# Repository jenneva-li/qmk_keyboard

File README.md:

# Split Keyboard

This is a fully customizable split mechanical keyboard featuring per-key RGB lighting, dual 2.2″ LCD displays, and complete QMK firmware support.

> **Note:** This project is currently under development. Detailed build instructions and documentation will be provided soon.

## Features

- **Ergonomic Split Layout** – Improves typing comfort and reduces strain.  
- **Dual LCD Displays** – Each half includes a 2.2" LCD for customizable graphics and real-time system information.
- **QMK Firmware** – Fully programmable, with support for layers, macros, and custom keymaps.  
- **Per-Key RGB Lighting** – Individually addressable SK6812 Mini LEDs for lighting effects.  
- **Hot-Swappable Switches** – Easily swap switches without soldering.  

## Specifications

- **Microcontroller**: STM32G474CETx
- **Key Layout**: Split layout with additional keys for layers and macros.
- **Display**: 2.2" LCD (320x240 resolution) per half.
- **Lighting**: SK6812 Mini RGB LEDs.
- **Switches**: Kailh Choc Low Profile.

## Build & Assembly

1. Order the PCBs and have them assembled using the provided BOM and pick-and-place files (e.g., via PCBWay).
2. 3D print the keyboard case components and source all necessary hardware, including LCDs, switches, keycaps, and mounting hardware.
3. Assemble all components, ensuring proper alignment of the PCB, switches, and case.
4. Flash the appropriate firmware onto each half of the keyboard. Note that the left and right halves require separate firmware builds.

## Roadmap
> This section outlines the planned features and improvements for the project. It is a work in progress and will be updated as development continues.

- [ ] Finalize PCB design  
- [ ] Publish detailed step-by-step build guide  
- [ ] Write firmware flashing and setup documentation  
- [ ] Upload STL files for 3D-printable case components  
- [ ] Publish demo and assembly videos

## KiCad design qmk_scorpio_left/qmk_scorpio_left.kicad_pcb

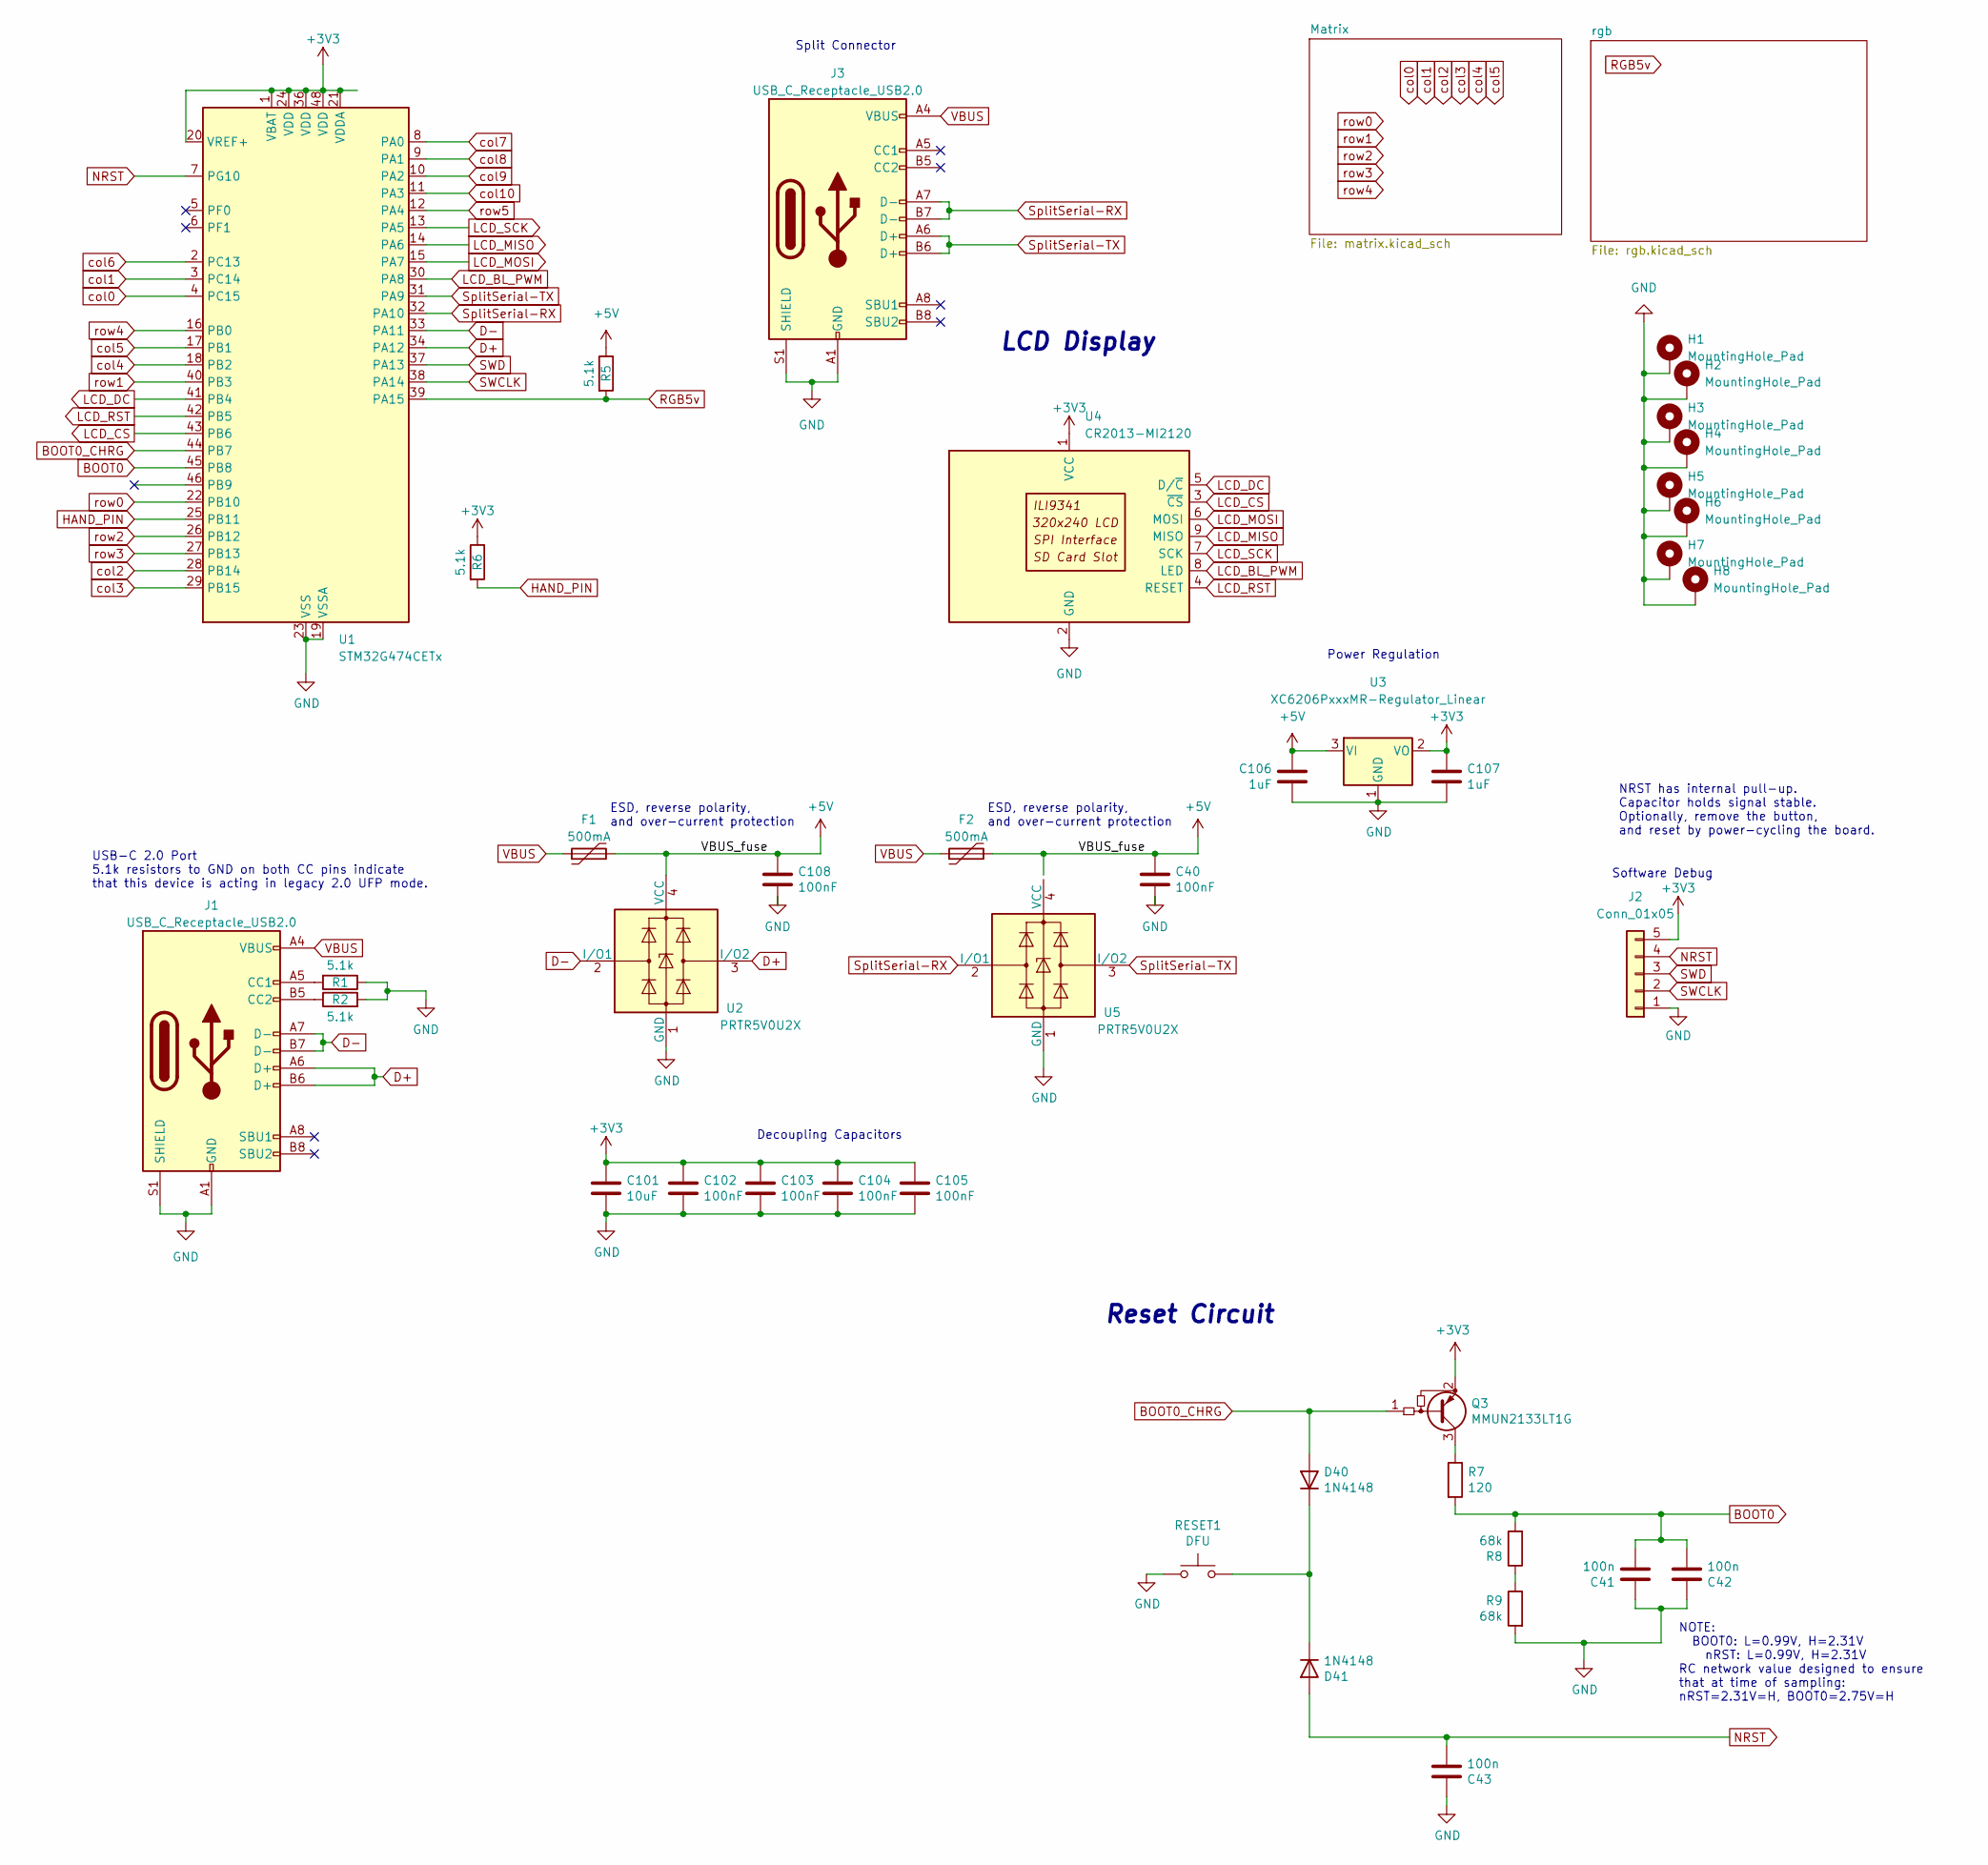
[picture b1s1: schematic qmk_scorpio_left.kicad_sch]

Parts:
C40, C102, C103, C104, C105, C108: 100nF; C_0402_1005Metric; LCSC C307331
C41, C42, C43: 100n; C_0805_2012Metric
C101: 10uF; C_0603_1608Metric; LCSC C307331
C106, C107: 1uF; C_0402_1005Metric; LCSC C307331
D40, D41: 1N4148; D_SOD-123
F1, F2: 500mA; Fuse_1206_3216Metric; LCSC C135341
H1, H2, H3, H4, H5, H6, H7, H8: MountingHole_Pad; MountingHole_3.2mm_M3_DIN965_Pad
J1, J3: USB_C_Receptacle_USB2.0; USB_C_Receptacle_HRO_TYPE-C-31-M-14; JlcRotOffset 180
J2: Conn_01x05; PinHeader_1x05_P2.54mm_Vertical
Q3: MMUN2133LT1G; SOT-23-3
R1, R2, R5, R6: 5.1k; R_0402_1005Metric
R7: 120; R_0805_2012Metric
R8, R9: 68k; R_0805_2012Metric
RESET1: DFU; SW_SPST_TL3342
U1: STM32G474CETx; LQFP-48_7x7mm_P0.5mm
U2, U5: PRTR5V0U2X; SOT-143; LCSC C2827688
U3: XC6206PxxxMR-Regulator_Linear; SOT-23; LCSC C5446
U4: CR2013-MI2120

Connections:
+3V3: C101.1, C102.1, C103.1, C104.1, C105.1, C107.1, J2.5, Q3.2 (E), R6.1, U1.1 (VBAT), U1.20 (VREF+), U1.21 (VDDA), U1.24 (VDD), U1.36 (VDD), U1.48 (VDD), U3.2 (VO), U4.1 (VCC)
+5V: C40.1, C106.1, C108.1, F1.2, F2.2, R5.1, U2.4 (VCC), U3.3 (VI); also elsewhere on the board
BOOT0: C41.2, C42.2, R7.2, R8.2, U1.45 (PB8)
BOOT0_CHRG: D40.2 (A), Q3.1 (B), U1.44 (PB7)
D+: J1.A6 (D+), J1.B6 (D+), U1.34 (PA12), U2.3 (I/O2)
D-: J1.A7 (D-), J1.B7 (D-), U1.33 (PA11), U2.2 (I/O1)
GND: C40.2, C41.1, C42.1, C43.1, C101.2, C102.2, C103.2, C104.2, C105.2, C106.2, C107.2, C108.2, H1.1, H2.1, H3.1, H4.1, H5.1, H6.1, H7.1, H8.1, J1.A1 (GND), J1.A12 (GND), J1.B1 (GND), J1.B12 (GND), J1.S1 (SHIELD), J2.1, J3.A1 (GND), J3.A12 (GND), J3.B1 (GND), J3.B12 (GND), J3.S1 (SHIELD), R1.1, R2.2, R9.2, RESET1.1, U1.19 (VSSA), U1.23 (VSS), U1.35 (VSS), U1.47 (VSS), U2.1 (GND), U3.1 (GND), U4.2 (GND), U5.1 (GND); also elsewhere on the board
HAND_PIN: R6.2, U1.25 (PB11)
LCD_BL_PWM: U1.30 (PA8), U4.8 (LED)
LCD_CS: U1.43 (PB6), U4.3 (~CS)
LCD_DC: U1.41 (PB4), U4.5 (D/~C)
LCD_MISO: U1.14 (PA6), U4.9 (MISO)
LCD_MOSI: U1.15 (PA7), U4.6 (MOSI)
LCD_RST: U1.42 (PB5), U4.4 (RESET)
LCD_SCK: U1.13 (PA5), U4.7 (SCK)
NRST: C43.2, D41.2 (A), J2.4, U1.7 (PG10)
unnamed: D40.1 (K), D41.1 (K), RESET1.2
unnamed: J1.A5 (CC1), R1.2
unnamed: J1.B5 (CC2), R2.1
unnamed: Q3.3 (C), R7.1
unnamed: R8.1, R9.1
RGB5v: R5.2, U1.39 (PA15); also elsewhere on the board
SWCLK: J2.2, U1.38 (PA14)
SWD: J2.3, U1.37 (PA13)
SplitSerial-RX: J3.A7 (D-), J3.B7 (D-), U1.32 (PA10), U5.2 (I/O1)
SplitSerial-TX: J3.A6 (D+), J3.B6 (D+), U1.31 (PA9), U5.3 (I/O2)
VBUS: F1.1, F2.1, J1.A4 (VBUS), J1.A9 (VBUS), J1.B4 (VBUS), J1.B9 (VBUS), J3.A4 (VBUS), J3.A9 (VBUS), J3.B4 (VBUS), J3.B9 (VBUS)
col0: U1.4 (PC15); also elsewhere on the board
col1: U1.3 (PC14); also elsewhere on the board
col2: U1.28 (PB14); also elsewhere on the board
col3: U1.29 (PB15); also elsewhere on the board
col4: U1.18 (PB2); also elsewhere on the board
col5: U1.17 (PB1); also elsewhere on the board
col6: U1.2 (PC13)
col7: U1.8 (PA0)
col8: U1.9 (PA1)
col9: U1.10 (PA2)
col10: U1.11 (PA3)
row0: U1.22 (PB10); also elsewhere on the board
row1: U1.40 (PB3); also elsewhere on the board
row2: U1.26 (PB12); also elsewhere on the board
row3: U1.27 (PB13); also elsewhere on the board
row4: U1.16 (PB0); also elsewhere on the board
row5: U1.12 (PA4)

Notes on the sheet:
Decoupling Capacitors
NOTE: BOOT0: L=0.99V, H=2.31V nRST: L=0.99V, H=2.31V RC network value designed to ensure that at time of sampling: nRST=2.31V=H, BOOT0=2.75V=H
Power Regulation
Reset Circuit
USB-C 2.0 Port 5.1k resistors to GND on both CC pins indicate that this device is acting in legacy 2.0 UFP mode.
ESD, reverse polarity, and over-current protection
Split Connector
Software Debug
NRST has internal pull-up. Capacitor holds signal stable. Optionally, remove the button, and reset by power-cycling the board.
LCD Display

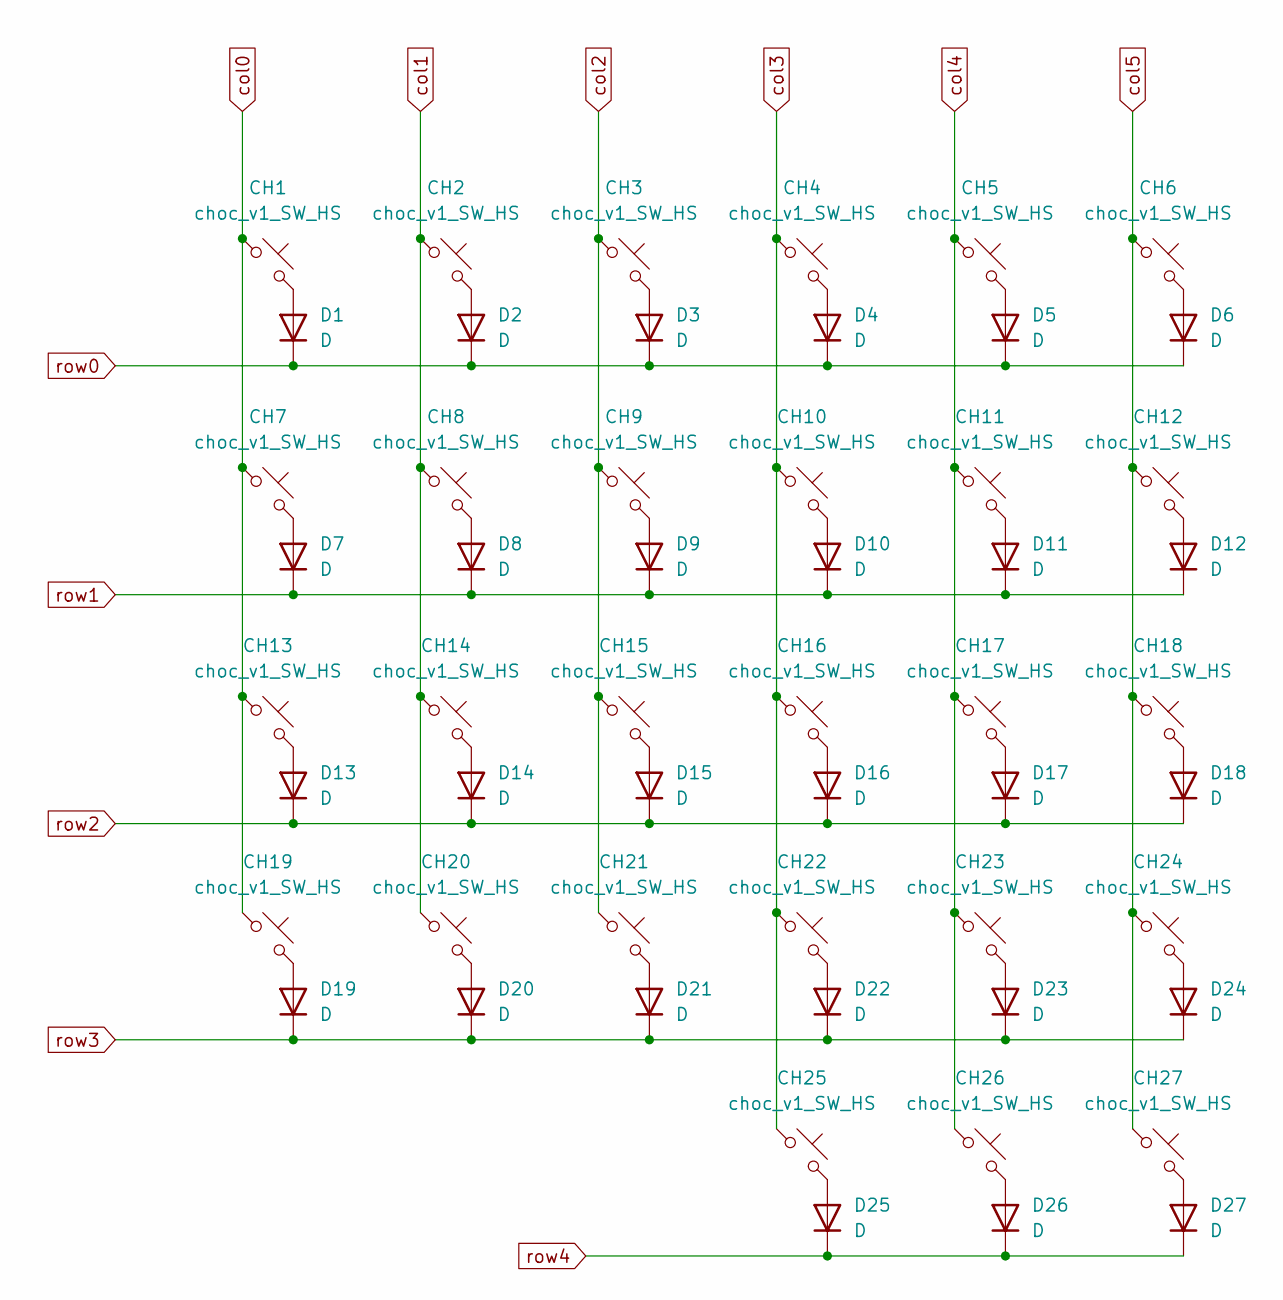
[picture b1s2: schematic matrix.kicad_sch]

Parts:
CH1, CH3, CH4, CH5, CH6, CH7, CH9, CH10, CH11, CH12, CH13, CH15, CH16, CH17, CH18, CH19, CH21, CH22, CH23, CH24, CH25, CH26, CH27: choc_v1_SW_HS; SW_choc_v1_HS_CPG135001S30_1u
CH2, CH8, CH14, CH20: choc_v1_SW_HS; SW_choc_v1_HS_CPG135001S30_1.5u
D1, D2, D3, D4, D5, D6, D7, D8, D9, D10, D11, D12, D13, D14, D15, D16, D17, D18, D19, D20, D21, D22, D23, D24, D25, D26, D27: D; D_SOD-123

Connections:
unnamed: CH1.2, D1.2 (A)
unnamed: CH2.2, D2.2 (A)
unnamed: CH3.2, D3.2 (A)
unnamed: CH4.2, D4.2 (A)
unnamed: CH5.2, D5.2 (A)
unnamed: CH6.2, D6.2 (A)
unnamed: CH7.2, D7.2 (A)
unnamed: CH8.2, D8.2 (A)
unnamed: CH9.2, D9.2 (A)
unnamed: CH10.2, D10.2 (A)
unnamed: CH11.2, D11.2 (A)
unnamed: CH12.2, D12.2 (A)
unnamed: CH13.2, D13.2 (A)
unnamed: CH14.2, D14.2 (A)
unnamed: CH15.2, D15.2 (A)
unnamed: CH16.2, D16.2 (A)
unnamed: CH17.2, D17.2 (A)
unnamed: CH18.2, D18.2 (A)
unnamed: CH19.2, D19.2 (A)
unnamed: CH20.2, D20.2 (A)
unnamed: CH21.2, D21.2 (A)
unnamed: CH22.2, D22.2 (A)
unnamed: CH23.2, D23.2 (A)
unnamed: CH24.2, D24.2 (A)
unnamed: CH25.2, D25.2 (A)
unnamed: CH26.2, D26.2 (A)
unnamed: CH27.2, D27.2 (A)
col0: CH1.1, CH7.1, CH13.1, CH19.1; also elsewhere on the board
col1: CH2.1, CH8.1, CH14.1, CH20.1; also elsewhere on the board
col2: CH3.1, CH9.1, CH15.1, CH21.1; also elsewhere on the board
col3: CH4.1, CH10.1, CH16.1, CH22.1, CH25.1; also elsewhere on the board
col4: CH5.1, CH11.1, CH17.1, CH23.1, CH26.1; also elsewhere on the board
col5: CH6.1, CH12.1, CH18.1, CH24.1, CH27.1; also elsewhere on the board
row0: D1.1 (K), D2.1 (K), D3.1 (K), D4.1 (K), D5.1 (K), D6.1 (K); also elsewhere on the board
row1: D7.1 (K), D8.1 (K), D9.1 (K), D10.1 (K), D11.1 (K), D12.1 (K); also elsewhere on the board
row2: D13.1 (K), D14.1 (K), D15.1 (K), D16.1 (K), D17.1 (K), D18.1 (K); also elsewhere on the board
row3: D19.1 (K), D20.1 (K), D21.1 (K), D22.1 (K), D23.1 (K), D24.1 (K); also elsewhere on the board
row4: D25.1 (K), D26.1 (K), D27.1 (K); also elsewhere on the board

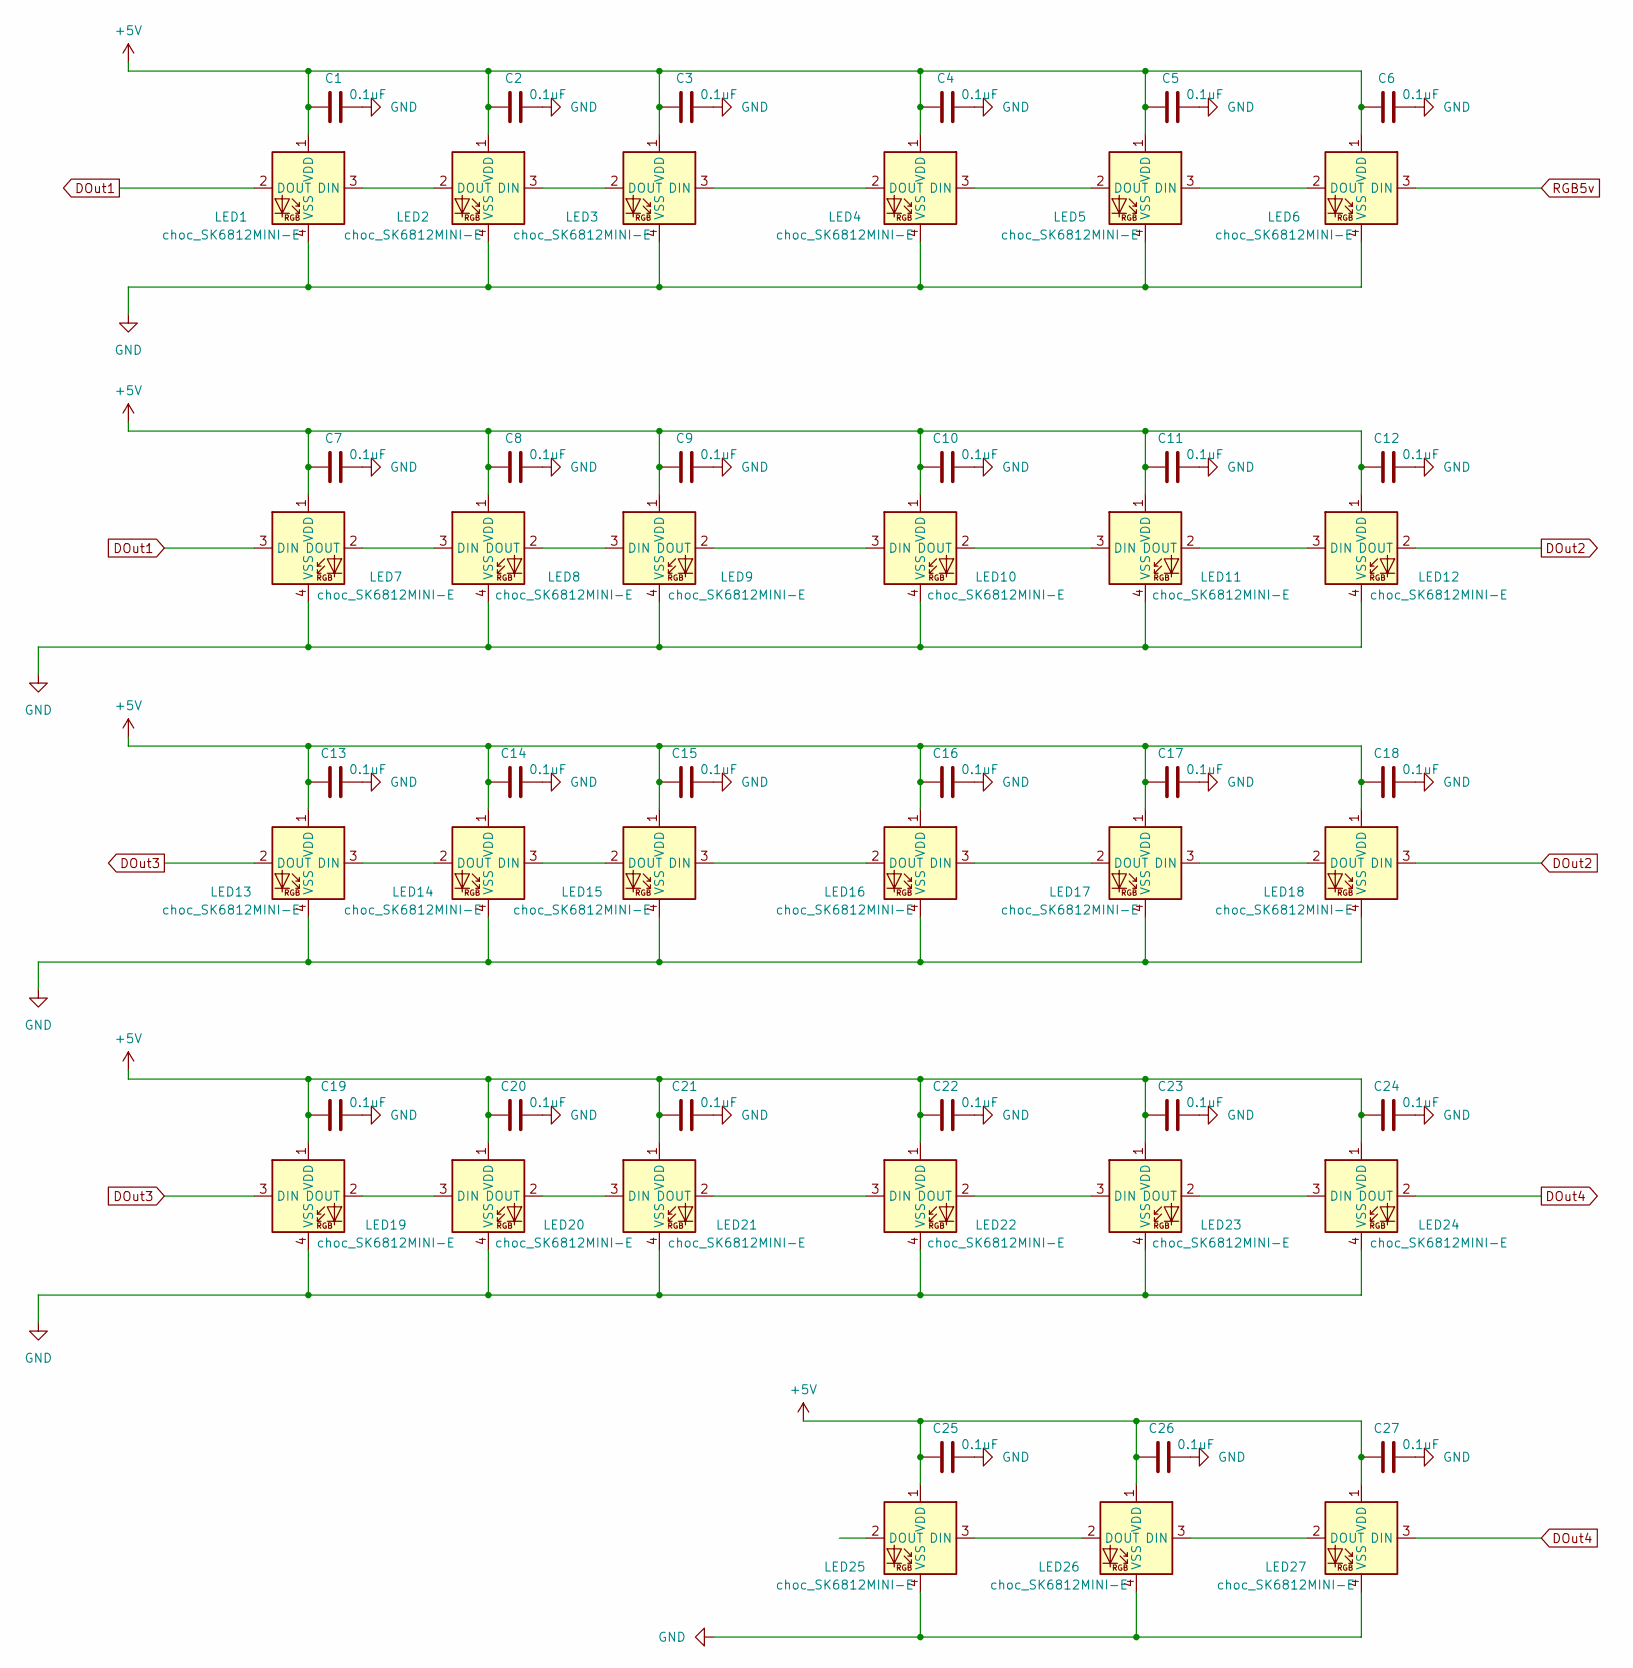
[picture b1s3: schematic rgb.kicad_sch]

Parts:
C1, C2, C3, C4, C5, C6, C7, C8, C9, C10, C11, C12, C13, C14, C15, C16, C17, C18, C19, C20, C21, C22, C23, C24, C25, C26, C27: 0.1uF; C_0402_1005Metric
LED1, LED2, LED3, LED4, LED5, LED6, LED7, LED8, LED9, LED10, LED11, LED12, LED13, LED14, LED15, LED16, LED17, LED18, LED19, LED20, LED21, LED22, LED23, LED24, LED25, LED26, LED27: choc_SK6812MINI-E; LED_choc_6028R

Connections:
+5V: C1.1, C2.1, C3.1, C4.1, C5.1, C6.1, C7.1, C8.1, C9.1, C10.1, C11.1, C12.1, C13.1, C14.1, C15.1, C16.1, C17.1, C18.1, C19.1, C20.1, C21.1, C22.1, C23.1, C24.1, C25.1, C26.1, C27.1, LED1.1 (VDD), LED2.1 (VDD), LED3.1 (VDD), LED4.1 (VDD), LED5.1 (VDD), LED6.1 (VDD), LED7.1 (VDD), LED8.1 (VDD), LED9.1 (VDD), LED10.1 (VDD), LED11.1 (VDD), LED12.1 (VDD), LED13.1 (VDD), LED14.1 (VDD), LED15.1 (VDD), LED16.1 (VDD), LED17.1 (VDD), LED18.1 (VDD), LED19.1 (VDD), LED20.1 (VDD), LED21.1 (VDD), LED22.1 (VDD), LED23.1 (VDD), LED24.1 (VDD), LED25.1 (VDD), LED26.1 (VDD), LED27.1 (VDD); also elsewhere on the board
DOut1: LED1.2 (DOUT), LED7.3 (DIN)
DOut2: LED12.2 (DOUT), LED18.3 (DIN)
DOut3: LED13.2 (DOUT), LED19.3 (DIN)
DOut4: LED24.2 (DOUT), LED27.3 (DIN)
GND: C1.2, C2.2, C3.2, C4.2, C5.2, C6.2, C7.2, C8.2, C9.2, C10.2, C11.2, C12.2, C13.2, C14.2, C15.2, C16.2, C17.2, C18.2, C19.2, C20.2, C21.2, C22.2, C23.2, C24.2, C25.2, C26.2, C27.2, LED1.4 (VSS), LED2.4 (VSS), LED3.4 (VSS), LED4.4 (VSS), LED5.4 (VSS), LED6.4 (VSS), LED7.4 (VSS), LED8.4 (VSS), LED9.4 (VSS), LED10.4 (VSS), LED11.4 (VSS), LED12.4 (VSS), LED13.4 (VSS), LED14.4 (VSS), LED15.4 (VSS), LED16.4 (VSS), LED17.4 (VSS), LED18.4 (VSS), LED19.4 (VSS), LED20.4 (VSS), LED21.4 (VSS), LED22.4 (VSS), LED23.4 (VSS), LED24.4 (VSS), LED25.4 (VSS), LED26.4 (VSS), LED27.4 (VSS); also elsewhere on the board
unnamed: LED1.3 (DIN), LED2.2 (DOUT)
unnamed: LED2.3 (DIN), LED3.2 (DOUT)
unnamed: LED3.3 (DIN), LED4.2 (DOUT)
unnamed: LED4.3 (DIN), LED5.2 (DOUT)
unnamed: LED5.3 (DIN), LED6.2 (DOUT)
unnamed: LED7.2 (DOUT), LED8.3 (DIN)
unnamed: LED8.2 (DOUT), LED9.3 (DIN)
unnamed: LED9.2 (DOUT), LED10.3 (DIN)
unnamed: LED10.2 (DOUT), LED11.3 (DIN)
unnamed: LED11.2 (DOUT), LED12.3 (DIN)
unnamed: LED13.3 (DIN), LED14.2 (DOUT)
unnamed: LED14.3 (DIN), LED15.2 (DOUT)
unnamed: LED15.3 (DIN), LED16.2 (DOUT)
unnamed: LED16.3 (DIN), LED17.2 (DOUT)
unnamed: LED17.3 (DIN), LED18.2 (DOUT)
unnamed: LED19.2 (DOUT), LED20.3 (DIN)
unnamed: LED20.2 (DOUT), LED21.3 (DIN)
unnamed: LED21.2 (DOUT), LED22.3 (DIN)
unnamed: LED22.2 (DOUT), LED23.3 (DIN)
unnamed: LED23.2 (DOUT), LED24.3 (DIN)
unnamed: LED25.3 (DIN), LED26.2 (DOUT)
unnamed: LED26.3 (DIN), LED27.2 (DOUT)
RGB5v: LED6.3 (DIN); also elsewhere on the board

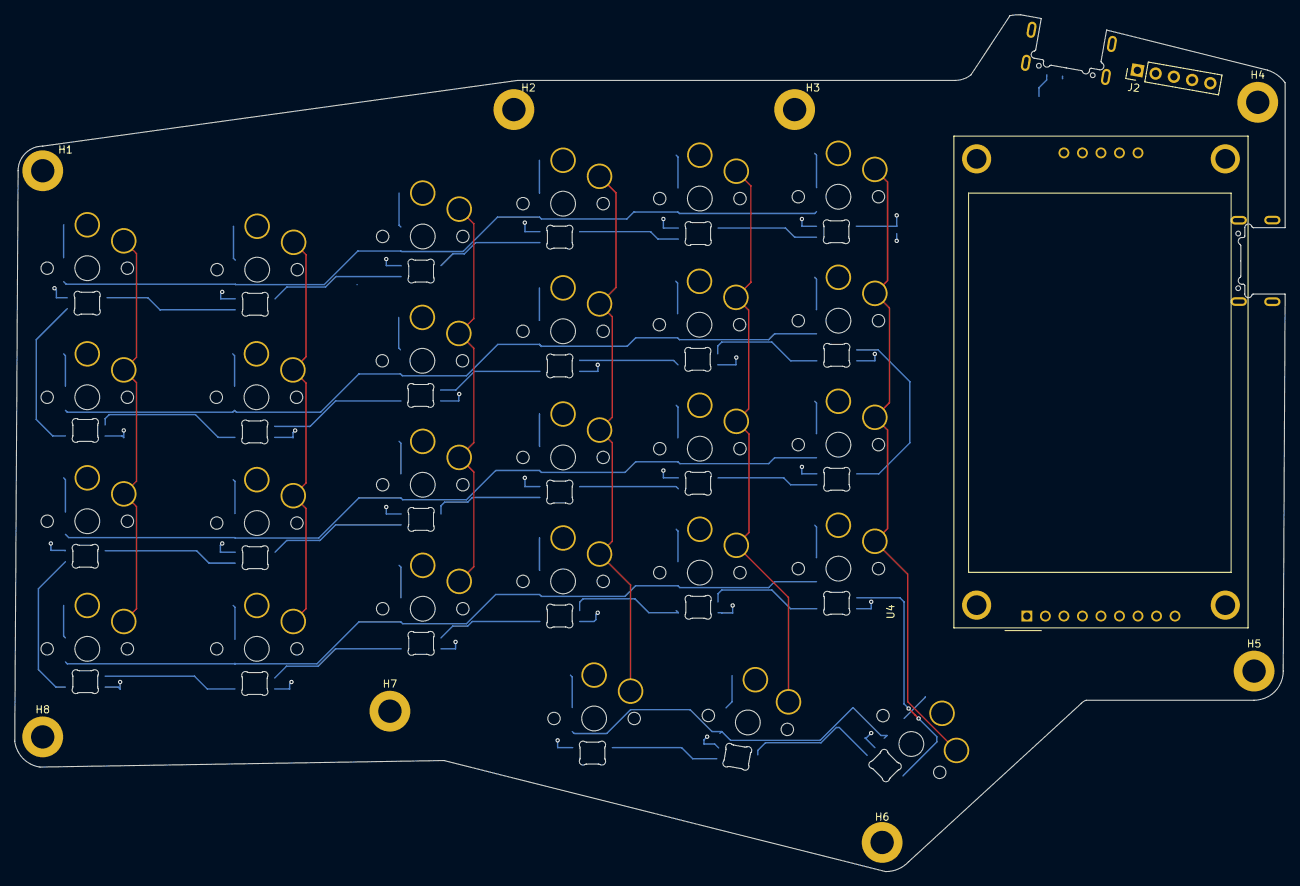
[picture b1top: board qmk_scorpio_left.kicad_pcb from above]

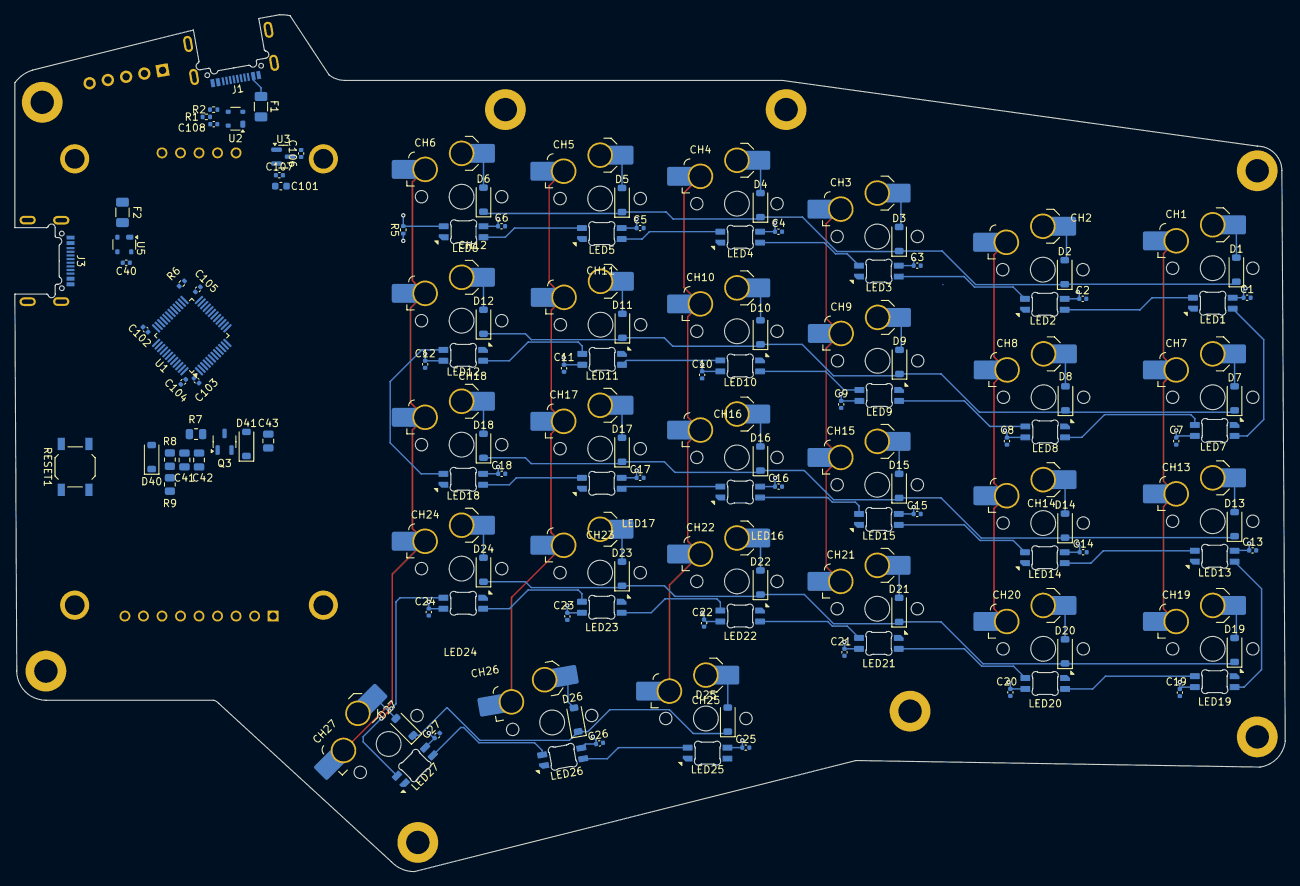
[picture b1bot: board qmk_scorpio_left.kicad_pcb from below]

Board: 2 copper layers, 174.2 x 117.5 mm, 149 parts (139 on the bottom side), 91 nets.

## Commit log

2025-07-06 add KiCAD project files
2025-07-06 pin corrections and updated rgb
2025-08-04 placed all components on board
2025-08-04 deleted prev board
2025-08-04 Rename qmk_scorpio.jpg to qmk_scorpio_initial_layout.jpg
2025-08-04 Rename qmk_scorpio.json to qmk_scorpio_initial_layout.json
2025-08-04 fixed annular width drc error
    increased pad diameter from 3.3 mm to 3.5 mm
2025-08-06 fixed col/row connections in matrix schematics
2025-08-08 keys routed
2025-08-11 placed 5V vias
2025-09-07 Restructure repo: add img/ folder for images
2025-09-08 Create README
    Added initial README with project overview, features, specifications, build instructions, and roadmap.
